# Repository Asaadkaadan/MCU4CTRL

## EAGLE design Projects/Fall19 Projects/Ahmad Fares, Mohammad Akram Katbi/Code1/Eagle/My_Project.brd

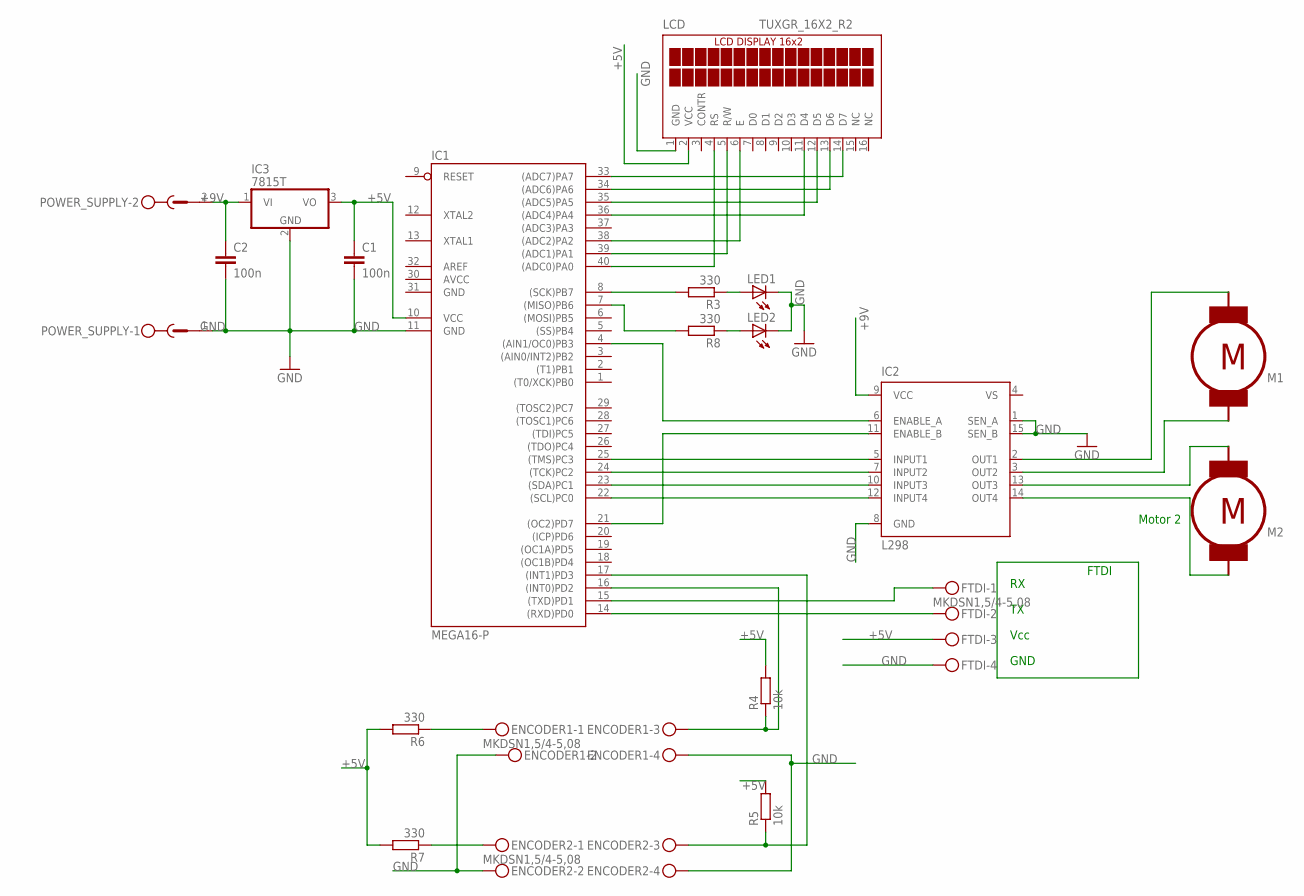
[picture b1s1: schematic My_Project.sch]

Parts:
C1, C2: 100n; C2.5-3
ENCODER1, ENCODER2: MKDSN1,5/4-5,08
FTDI: MKDSN1,5/4-5,08
IC1: MEGA16-P; DIL40; MPN ATMEGA16-16PU
IC2: L298; MULTIWATT-15
IC3: 7815T; TO220H
LCD: TUXGR_16X2_R2
LED1, LED2: LEDLZR181; LZR181
M1, M2: MOTOR_DC_EINFACH_XL; 2PIN
POWER_SUPPLY: MSTBV2
R3, R6, R7, R8: 330; 0207/10
R4, R5: 10k; 0207/10

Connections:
+5V: C1.1, FTDI.3, IC1.10 (VCC), IC3.3 (VO), LCD.2 (VCC), R4.2, R5.2, R6.2, R7.2
+9V: C2.1, IC2.9 (VCC), IC3.1 (VI), POWER_SUPPLY.2
AVCC: IC1.30 (AVCC)
GND: C1.2, C2.2, ENCODER1.2, ENCODER1.4, ENCODER2.2, ENCODER2.4, FTDI.4, IC1.11 (GND), IC1.31 (GND), IC2.1 (SEN_A), IC2.8 (GND), IC2.15 (SEN_B), IC3.2 (GND), LCD.1 (GND), LED1.K (C), LED2.K (C), POWER_SUPPLY.1
unnamed: IC1.33 ((ADC7)PA7), LCD.14 (D7)
unnamed: IC1.34 ((ADC6)PA6), LCD.13 (D6)
unnamed: IC1.35 ((ADC5)PA5), LCD.12 (D5)
unnamed: IC1.36 ((ADC4)PA4), LCD.11 (D4)
unnamed: IC1.38 ((ADC2)PA2), LCD.6 (E)
unnamed: IC1.39 ((ADC1)PA1), LCD.5 (R/W)
unnamed: IC1.40 ((ADC0)PA0), LCD.4 (RS)
unnamed: IC1.4 ((AIN1/OC0)PB3), IC2.6 (ENABLE_A)
unnamed: IC1.21 ((OC2)PD7), IC2.11 (ENABLE_B)
unnamed: IC1.7 ((MISO)PB6), R8.2
unnamed: IC1.25 ((TMS)PC3), IC2.5 (INPUT1)
unnamed: IC1.24 ((TCK)PC2), IC2.7 (INPUT2)
unnamed: IC1.23 ((SDA)PC1), IC2.10 (INPUT3)
unnamed: IC1.22 ((SCL)PC0), IC2.12 (INPUT4)
unnamed: IC1.8 ((SCK)PB7), R3.2
unnamed: LED1.A, R3.1
unnamed: LED2.A, R8.1
unnamed: IC2.2 (OUT1), M1.1 (R1)
unnamed: IC2.3 (OUT2), M1.2 (R2)
unnamed: IC2.13 (OUT3), M2.1 (R1)
unnamed: IC2.14 (OUT4), M2.2 (R2)
unnamed: ENCODER1.1, R6.1
unnamed: ENCODER1.3, IC1.16 ((INT0)PD2), R4.1
unnamed: ENCODER2.3, IC1.17 ((INT1)PD3), R5.1
unnamed: ENCODER2.1, R7.1
RX: FTDI.2, IC1.14 ((RXD)PD0)
TX: FTDI.1, IC1.15 ((TXD)PD1)
VS: IC2.4 (VS)

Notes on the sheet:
Vcc
GND
FTDI
Motor 2

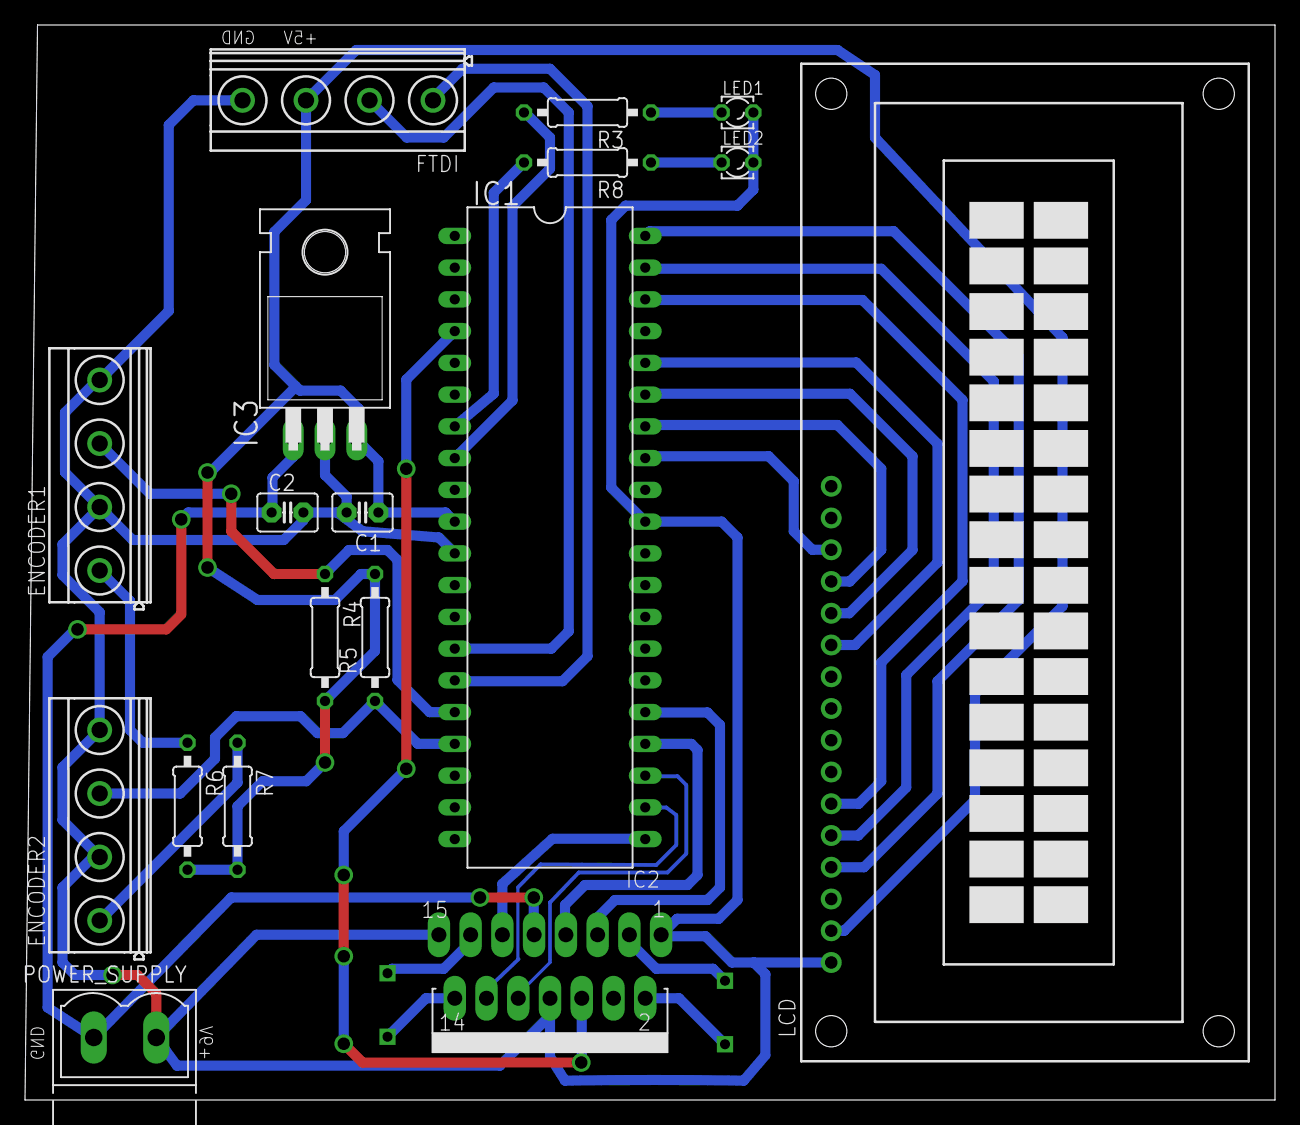
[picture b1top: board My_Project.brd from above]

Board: 2 copper layers, 100.0 x 86.0 mm, 20 parts (0 on the bottom side), 30 nets.

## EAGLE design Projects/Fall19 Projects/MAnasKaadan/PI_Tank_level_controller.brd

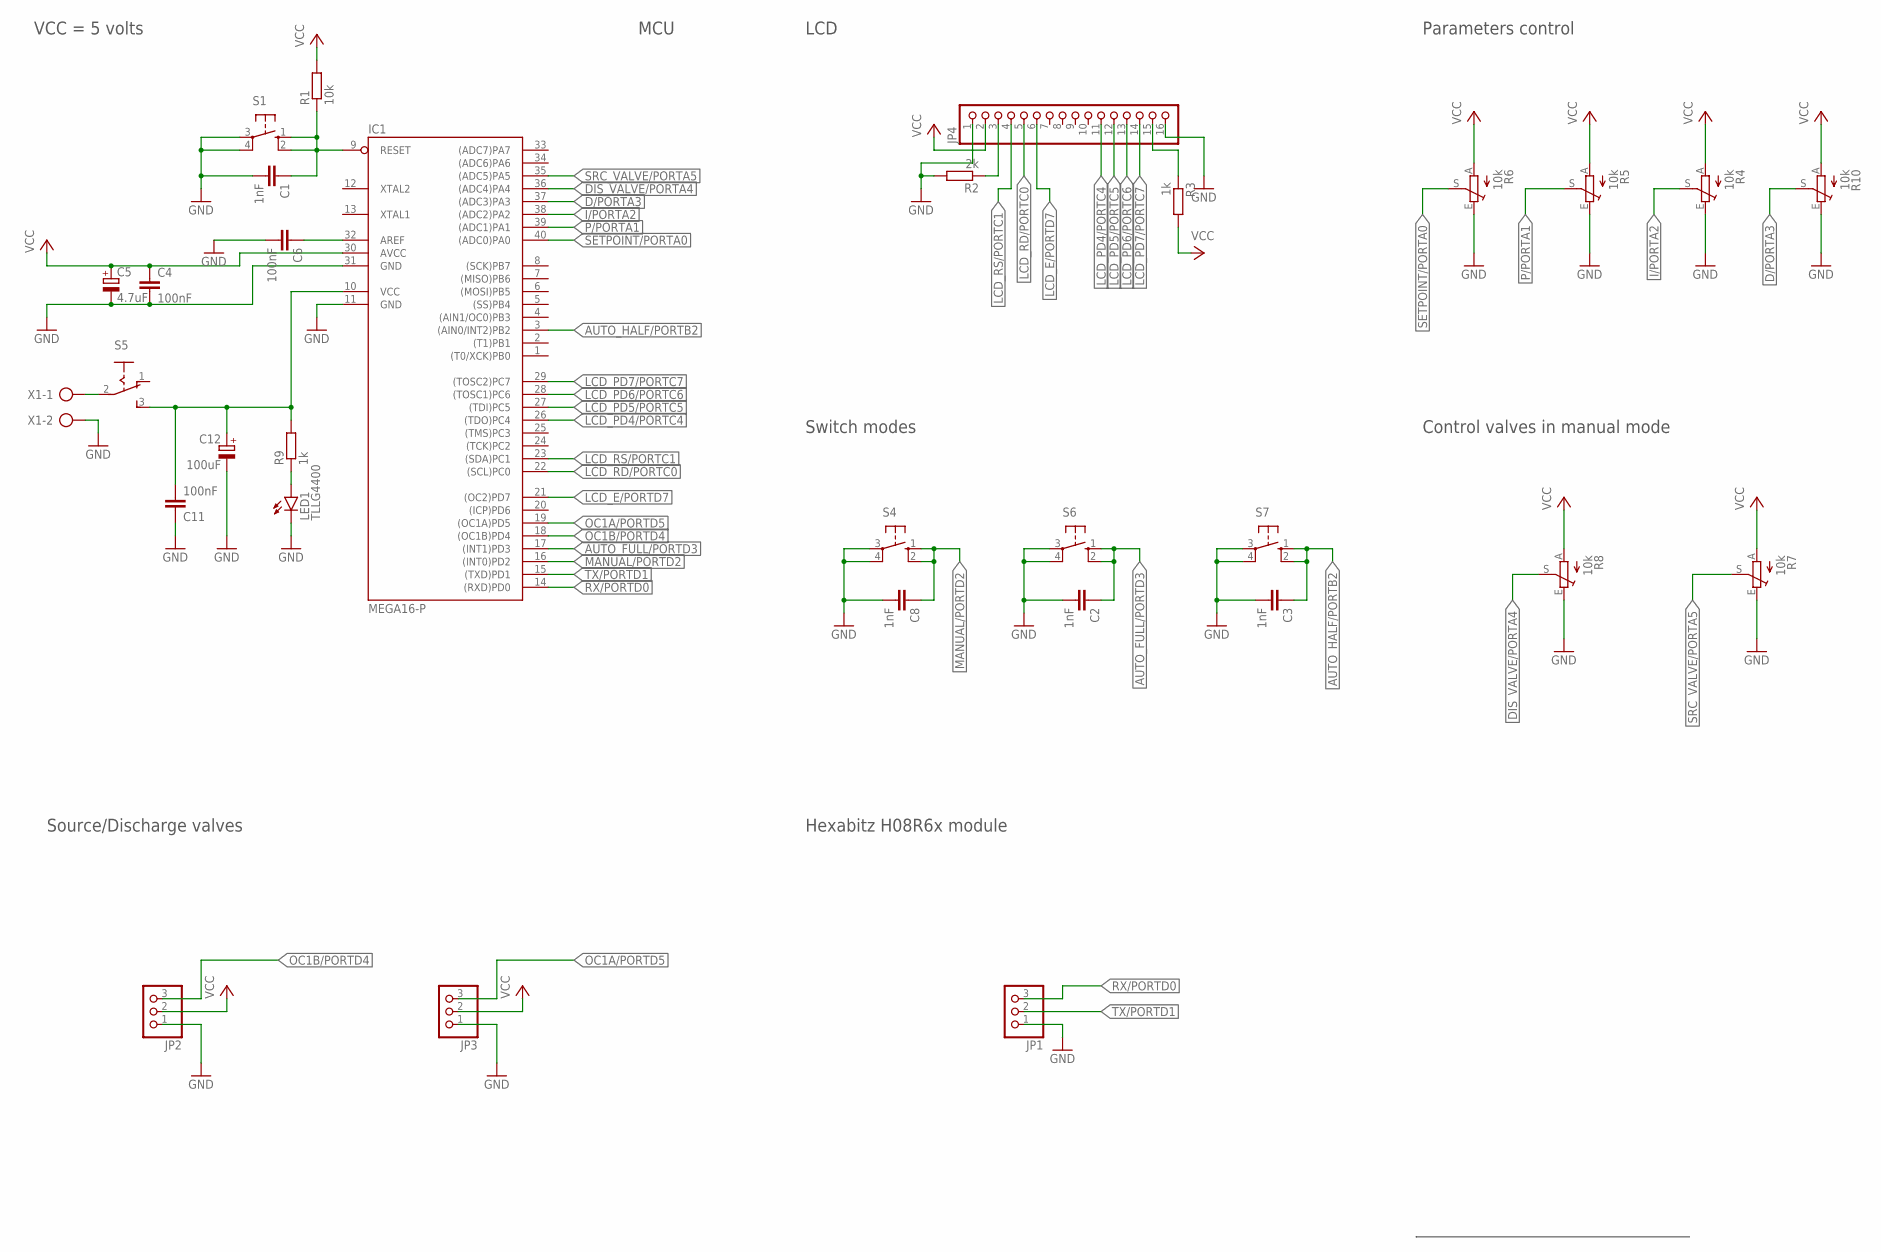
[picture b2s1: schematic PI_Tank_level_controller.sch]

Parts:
C1, C2, C3, C8: 1nF; C025-024X044
C4, C6, C11: 100nF; C025-024X044
C5: 4.7uF; E2,5-6E
C12: 100uF; B45181A
IC1: MEGA16-P; DIL40
JP1, JP2, JP3: PINHD-1X3; 1X03
JP4: PINHD-1X16; 1X16
LED1: TLLG4400; LED3MM
R1: 10k; 0204/7
R2: 2k; 0204/7
R3, R9: 1k; 0204/7
R4, R5, R6, R7, R8, R10: 10k; RJ9W
S1, S4, S6, S7: 10-XX; B3F-10XX
S5: 255SB
X1: AK300/2

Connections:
AUTO_FULL/PORTD3: C2.1, IC1.17 ((INT1)PD3), S6.1 (S), S6.2 (S1)
AUTO_HALF/PORTB2: C3.1, IC1.3 ((AIN0/INT2)PB2), S7.1 (S), S7.2 (S1)
D/PORTA3: IC1.37 ((ADC3)PA3), R10.S
DIS_VALVE/PORTA4: IC1.36 ((ADC4)PA4), R8.S
GND: C1.2, C2.2, C3.2, C4.2, C5.-, C6.2, C8.2, C11.1, C12.-, IC1.11 (GND), IC1.31 (GND), JP1.1, JP2.1, JP3.1, JP4.1, JP4.16, LED1.K (C), R2.2, R4.E, R5.E, R6.E, R7.E, R8.E, R10.E, S1.3, S1.4 (P1), S4.3, S4.4 (P1), S6.3, S6.4 (P1), S7.3, S7.4 (P1), X1.2
I/PORTA2: IC1.38 ((ADC2)PA2), R4.S
LCD_E/PORTD7: IC1.21 ((OC2)PD7), JP4.6
LCD_PD4/PORTC4: IC1.26 ((TDO)PC4), JP4.11
LCD_PD5/PORTC5: IC1.27 ((TDI)PC5), JP4.12
LCD_PD6/PORTC6: IC1.28 ((TOSC1)PC6), JP4.13
LCD_PD7/PORTC7: IC1.29 ((TOSC2)PC7), JP4.14
LCD_RD/PORTC0: IC1.22 ((SCL)PC0), JP4.5
LCD_RS/PORTC1: IC1.23 ((SDA)PC1), JP4.4
MANUAL/PORTD2: C8.1, IC1.16 ((INT0)PD2), S4.1 (S), S4.2 (S1)
unnamed: C1.1, IC1.9 (RESET), R1.1, S1.1 (S), S1.2 (S1)
unnamed: JP4.15, R3.1
unnamed: C6.1, IC1.32 (AREF)
unnamed: JP4.3, R2.1
unnamed: S5.2, X1.1
unnamed: LED1.A, R9.1
OC1A/PORTD5: IC1.19 ((OC1A)PD5), JP3.3
OC1B/PORTD4: IC1.18 ((OC1B)PD4), JP2.3
P/PORTA1: IC1.39 ((ADC1)PA1), R5.S
RX/PORTD0: IC1.14 ((RXD)PD0), JP1.3
SETPOINT/PORTA0: IC1.40 ((ADC0)PA0), R6.S
SRC_VALVE/PORTA5: IC1.35 ((ADC5)PA5), R7.S
TX/PORTD1: IC1.15 ((TXD)PD1), JP1.2
VCC: C4.1, C5.+, C11.2, C12.+, IC1.10 (VCC), IC1.30 (AVCC), JP2.2, JP3.2, JP4.2, R1.2, R3.2, R4.A, R5.A, R6.A, R7.A, R8.A, R9.2, R10.A, S5.3 (S)

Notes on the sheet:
VCC = 5 volts
MCU
LCD
Parameters control
Switch modes
Hexabitz H08R6x module
Source/Discharge valves
Control valves in manual mode

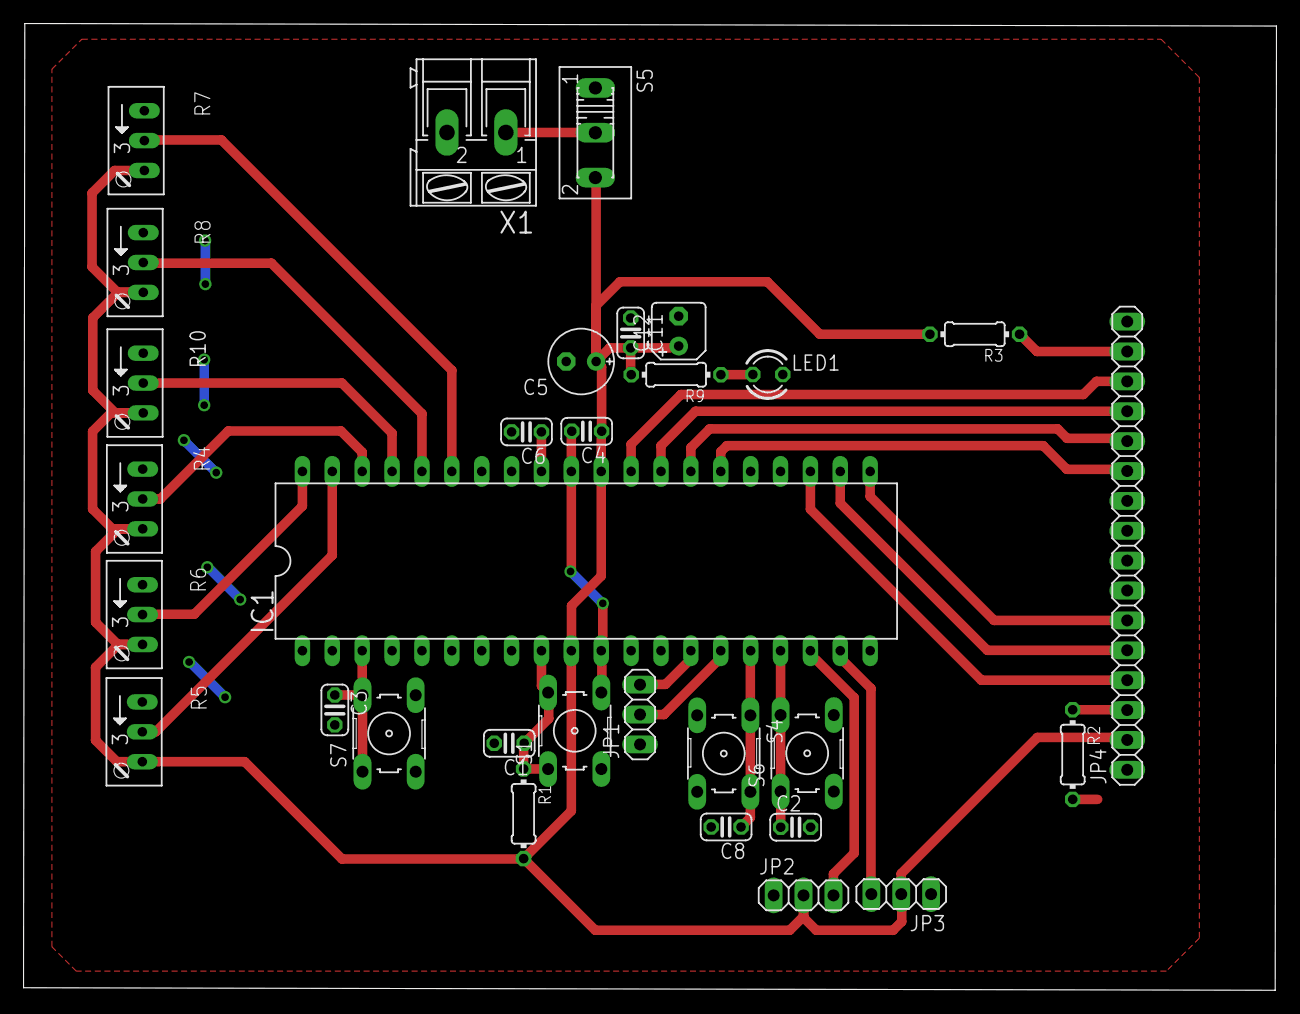
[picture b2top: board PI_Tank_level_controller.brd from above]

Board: 2 copper layers, 106.5 x 82.2 mm, 31 parts (0 on the bottom side), 28 nets.

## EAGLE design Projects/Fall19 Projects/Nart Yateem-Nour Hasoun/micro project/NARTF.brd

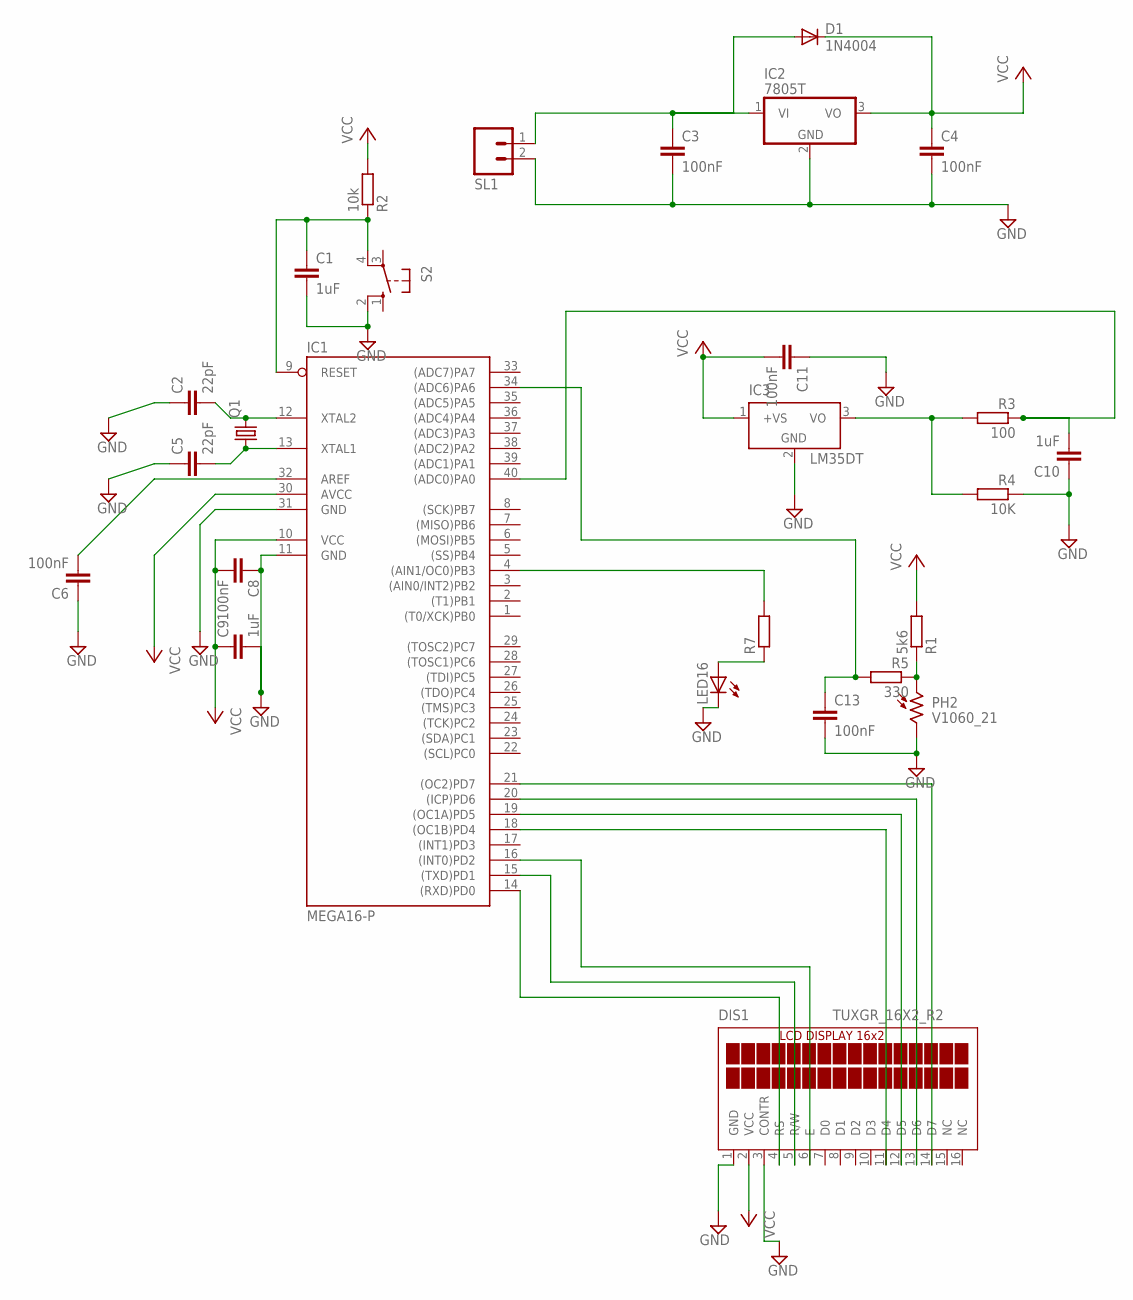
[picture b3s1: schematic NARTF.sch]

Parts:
C1, C9, C10: 1uF; C025-025X050
C2, C5: 22pF; C025-025X050
C3, C4, C6, C8, C11, C13: 100nF; C025-025X050
D1: 1N4004; DO41-10
DIS1: TUXGR_16X2_R2
IC1: MEGA16-P; DIL40
IC2: 7805T; TO220H
IC3: LM35DT; TO220V
LED16: LED3MM
PH2: V1060_21; TO-5_V10
Q1: CRYSTALHC49U70; HC49U70
R1: 5k6; 0207/7
R2: 10k; 0207/7
R3: 100; 0207/7
R4: 10K; 0207/7
R5: 330; 0207/7
R7: R-EU_0207/12; 0207/12
S2: 10-XX; B3F-10XX
SL1: M02; 02P

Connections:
GND: C1.2, C2.1, C3.2, C4.2, C5.1, C6.1, C8.1, C9.2, C10.1, C11.1, C13.2, DIS1.1 (GND), DIS1.3 (CONTR), IC1.11 (GND), IC1.31 (GND), IC2.2 (GND), IC3.2 (GND), LED16.K (C), PH2.2, R4.1, S2.2 (S1), SL1.2
unnamed: C1.1, IC1.9 (RESET), R2.1, S2.4 (P1)
unnamed: IC1.4 ((AIN1/OC0)PB3), R7.2
unnamed: C3.1, D1.A, IC2.1 (VI), SL1.1
unnamed: C2.2, IC1.12 (XTAL2), Q1.2
unnamed: C5.2, IC1.13 (XTAL1), Q1.1
unnamed: C6.2, IC1.32 (AREF)
unnamed: C13.1, IC1.34 ((ADC6)PA6), R5.2
unnamed: LED16.A, R7.1
unnamed: IC3.3 (VO), R3.2, R4.2
unnamed: DIS1.11 (D4), IC1.18 ((OC1B)PD4)
unnamed: C10.2, IC1.40 ((ADC0)PA0), R3.1
unnamed: DIS1.12 (D5), IC1.19 ((OC1A)PD5)
unnamed: DIS1.13 (D6), IC1.20 ((ICP)PD6)
unnamed: PH2.1, R1.1, R5.1
unnamed: DIS1.4 (RS), IC1.14 ((RXD)PD0)
unnamed: DIS1.5 (R/W), IC1.15 ((TXD)PD1)
unnamed: DIS1.6 (E), IC1.16 ((INT0)PD2)
NART-NOUR: DIS1.14 (D7), IC1.21 ((OC2)PD7)

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
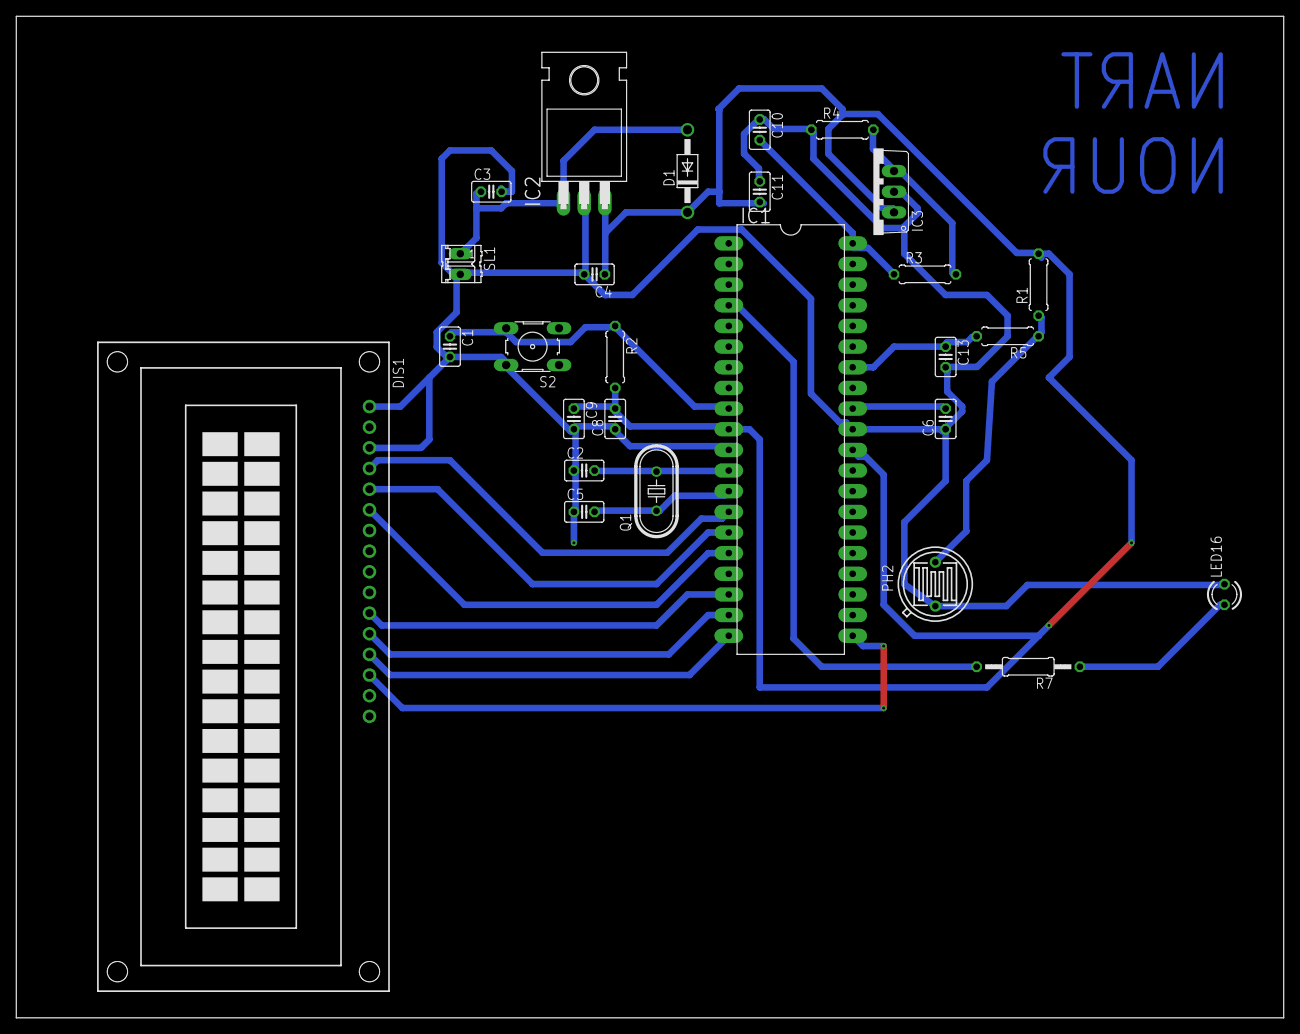
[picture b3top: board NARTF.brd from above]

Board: 2 copper layers, 155.9 x 123.2 mm, 27 parts (0 on the bottom side), 20 nets.

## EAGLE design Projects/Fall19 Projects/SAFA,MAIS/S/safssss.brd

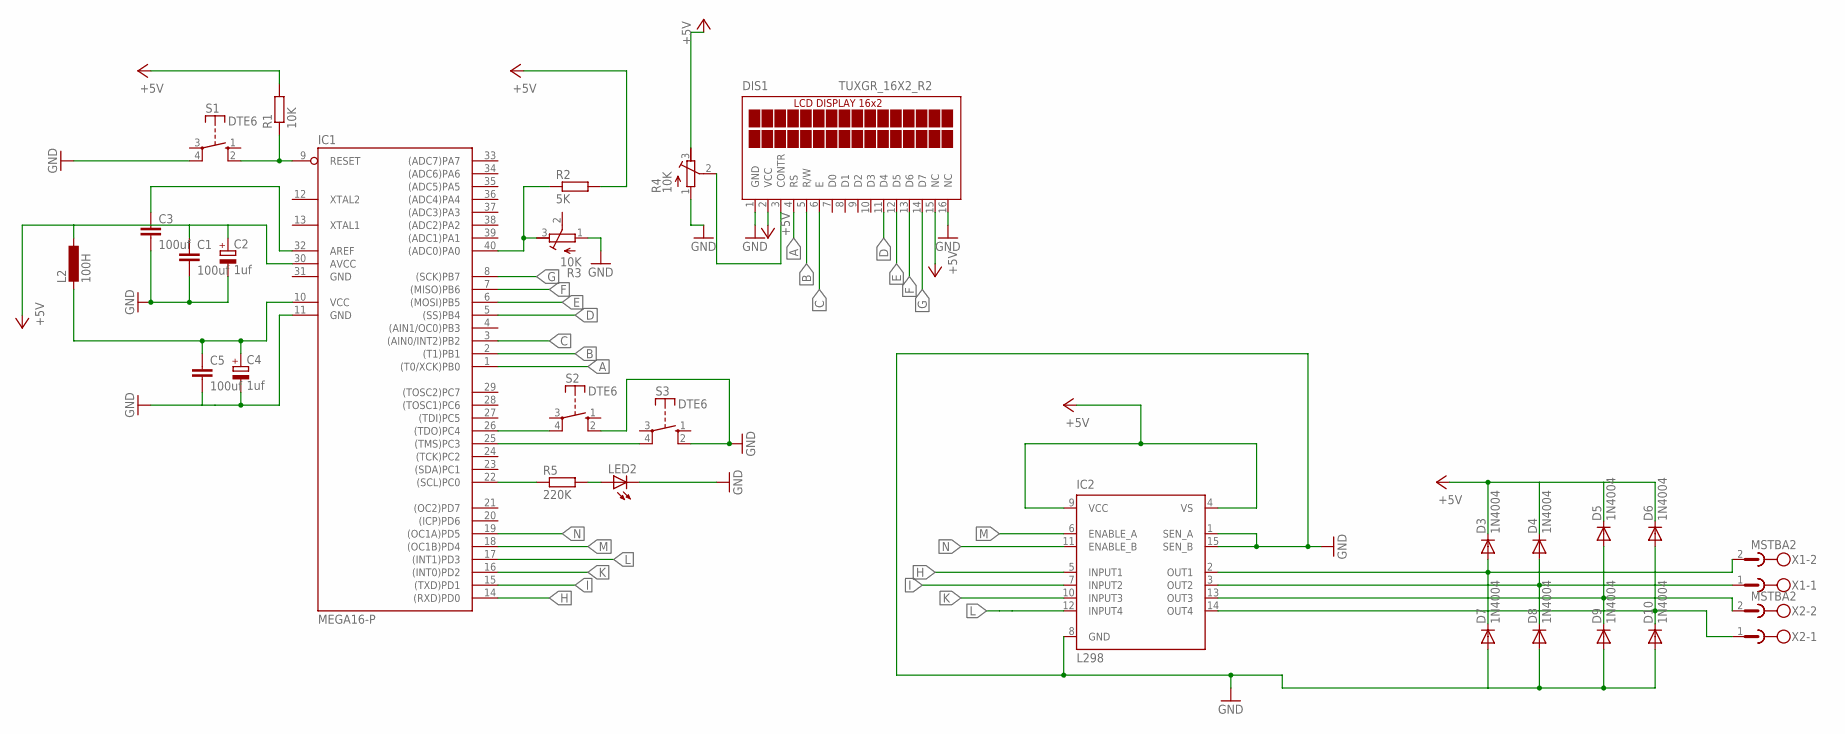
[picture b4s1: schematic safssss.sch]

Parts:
C1, C3, C5: 100uf; C025-024X044
C2, C4: 1uf; B45181A
D3, D4, D5, D6, D7, D8, D9, D10: 1N4004; DO41-10
DIS1: TUXGR_16X2_R2
IC1: MEGA16-P; DIL40
IC2: L298; MULTIWATT-15
L2: 100H; 0204V
LED2: LED3MM
R1: 10K; 0204V
R2: 5K; 0204V
R3, R4: 10K; RTRIM64Z
R5: 220K; 0204V
S1, S2, S3: DTE6
X1, X2: MSTBA2

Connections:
+5V: C1.1, C2.+, D3.C, D4.C, D5.C, D6.C, DIS1.2 (VCC), DIS1.15 (NC), IC1.30 (AVCC), IC2.4 (VS), IC2.9 (VCC), L2.1, R1.2, R2.2, R4.3 (E)
A: DIS1.4 (RS), IC1.1 ((T0/XCK)PB0)
B: DIS1.5 (R/W), IC1.2 ((T1)PB1)
C: DIS1.6 (E), IC1.3 ((AIN0/INT2)PB2)
D: DIS1.11 (D4), IC1.5 ((SS)PB4)
E: DIS1.12 (D5), IC1.6 ((MOSI)PB5)
F: DIS1.13 (D6), IC1.7 ((MISO)PB6)
G: DIS1.14 (D7), IC1.8 ((SCK)PB7)
GND: C1.2, C2.-, C3.2, C4.-, C5.2, D7.A, D8.A, D9.A, D10.A, DIS1.1 (GND), DIS1.16 (NC), IC1.11 (GND), IC1.31 (GND), IC2.1 (SEN_A), IC2.8 (GND), IC2.15 (SEN_B), LED2.K (C), R3.1 (A), R4.1 (A), S1.4, S2.2 (S), S3.2 (S)
H: IC1.14 ((RXD)PD0), IC2.5 (INPUT1)
I: IC1.15 ((TXD)PD1), IC2.7 (INPUT2)
K: IC1.16 ((INT0)PD2), IC2.10 (INPUT3)
L: IC1.17 ((INT1)PD3), IC2.12 (INPUT4)
M: IC1.18 ((OC1B)PD4), IC2.6 (ENABLE_A)
N: IC1.19 ((OC1A)PD5), IC2.11 (ENABLE_B)
unnamed: IC1.9 (RESET), R1.1, S1.2 (S)
unnamed: IC1.40 ((ADC0)PA0), R2.1, R3.3 (E)
unnamed: C3.1, IC1.32 (AREF)
unnamed: C4.+, C5.1, IC1.10 (VCC), L2.2
unnamed: DIS1.3 (CONTR), R4.2 (S)
unnamed: IC1.22 ((SCL)PC0), R5.1
unnamed: LED2.A, R5.2
unnamed: D3.A, D7.C, IC2.2 (OUT1), X1.2
unnamed: D4.A, D8.C, IC2.3 (OUT2), X1.1
unnamed: D5.A, D9.C, IC2.13 (OUT3), X2.2
unnamed: D6.A, D10.C, IC2.14 (OUT4), X2.1
unnamed: IC1.26 ((TDO)PC4), S2.4
unnamed: IC1.25 ((TMS)PC3), S3.4

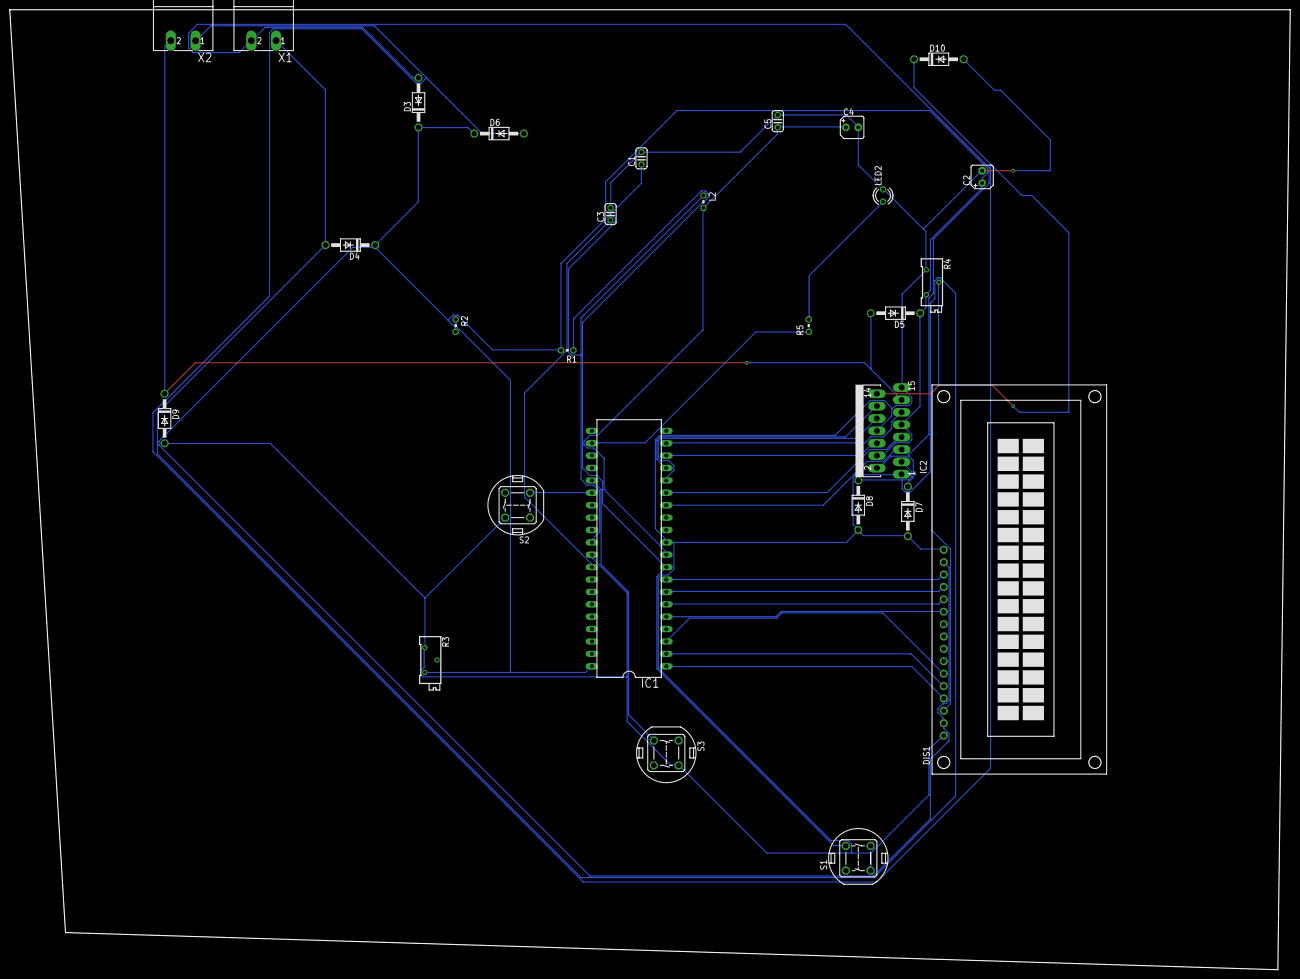
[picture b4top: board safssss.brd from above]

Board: 2 copper layers, 262.6 x 196.8 mm, 28 parts (0 on the bottom side), 28 nets.

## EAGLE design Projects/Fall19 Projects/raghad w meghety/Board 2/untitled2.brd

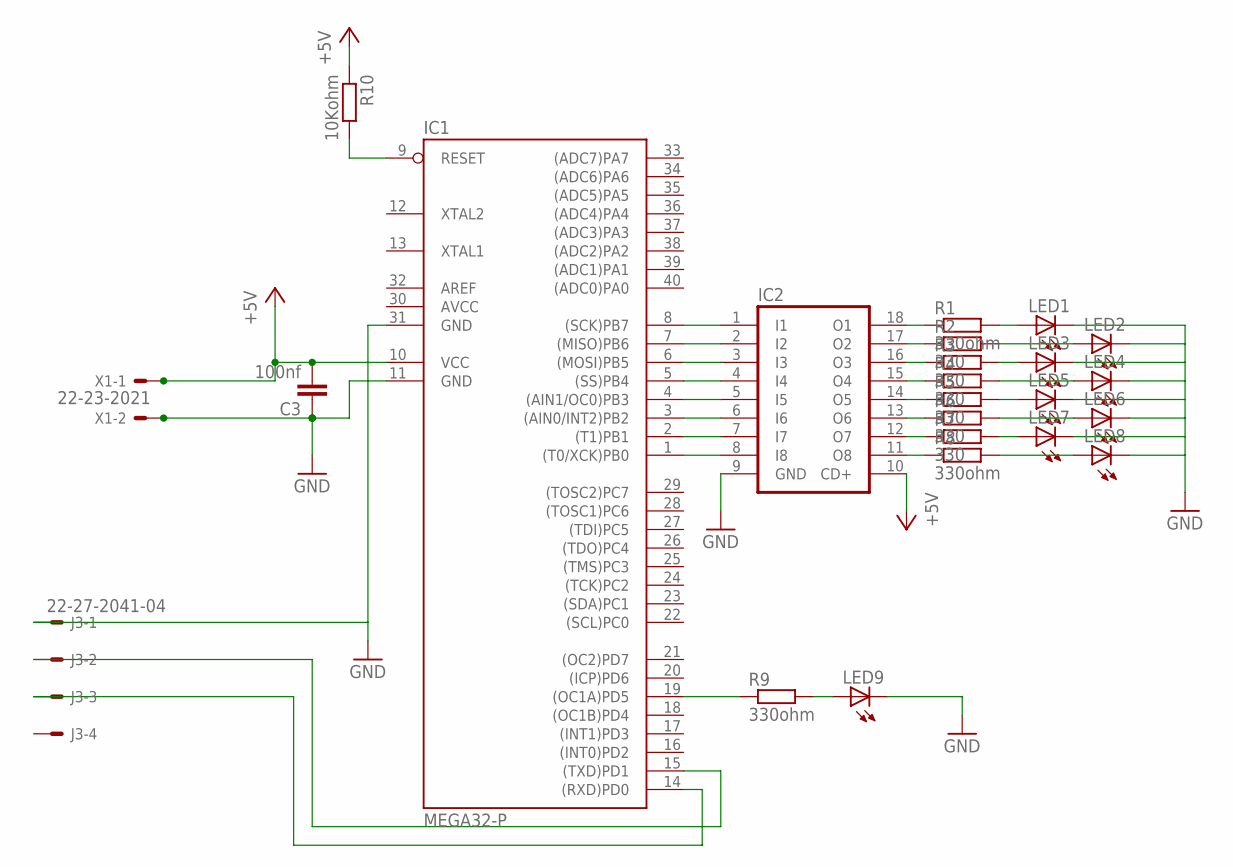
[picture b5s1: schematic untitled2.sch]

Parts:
C3: 100nf; C050-025X075
IC1: MEGA32-P; DIL40
IC2: ULN2803A; DIL18
J3: 22-27-2041-04; 6410-04
LED1, LED2, LED3, LED4, LED5, LED6, LED7, LED8, LED9: LEDIRL80A; IRL80A
R1, R8, R9: 330ohm; 0207/10
R2, R3, R4, R5, R6, R7: 330; 0207/10
R10: 10Kohm; 0207/10
X1: 22-23-2021

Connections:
AVCC: IC1.30 (AVCC)
unnamed: IC1.8 ((SCK)PB7), IC2.1 (I1)
unnamed: IC1.7 ((MISO)PB6), IC2.2 (I2)
unnamed: IC1.6 ((MOSI)PB5), IC2.3 (I3)
unnamed: IC1.5 ((SS)PB4), IC2.4 (I4)
unnamed: IC1.4 ((AIN1/OC0)PB3), IC2.5 (I5)
unnamed: IC1.3 ((AIN0/INT2)PB2), IC2.6 (I6)
unnamed: IC1.2 ((T1)PB1), IC2.7 (I7)
unnamed: IC1.1 ((T0/XCK)PB0), IC2.8 (I8)
unnamed: LED1.A, R1.2
unnamed: LED2.A, R2.2
unnamed: LED3.A, R3.2
unnamed: LED4.A, R4.2
unnamed: LED5.A, R5.2
unnamed: LED6.A, R6.2
unnamed: LED7.A, R7.2
unnamed: LED8.A, R8.2
unnamed: IC1.19 ((OC1A)PD5), R9.1
unnamed: LED9.A, R9.2
unnamed: IC1.9 (RESET), R10.2
unnamed: C3.2, IC1.10 (VCC), IC2.10 (CD+), R10.1, X1.1
unnamed: C3.1, IC1.11 (GND), IC1.31 (GND), IC2.9 (GND), J3.1, LED1.K (C), LED2.K (C), LED3.K (C), LED4.K (C), LED5.K (C), LED6.K (C), LED7.K (C), LED8.K (C), LED9.K (C), X1.2
unnamed: IC1.15 ((TXD)PD1), J3.2
unnamed: IC1.14 ((RXD)PD0), J3.3
unnamed: IC2.18 (O1), R1.1
unnamed: IC2.17 (O2), R2.1
unnamed: IC2.16 (O3), R3.1
unnamed: IC2.15 (O4), R4.1
unnamed: IC2.14 (O5), R5.1
unnamed: IC2.13 (O6), R6.1
unnamed: IC2.12 (O7), R7.1
unnamed: IC2.11 (O8), R8.1

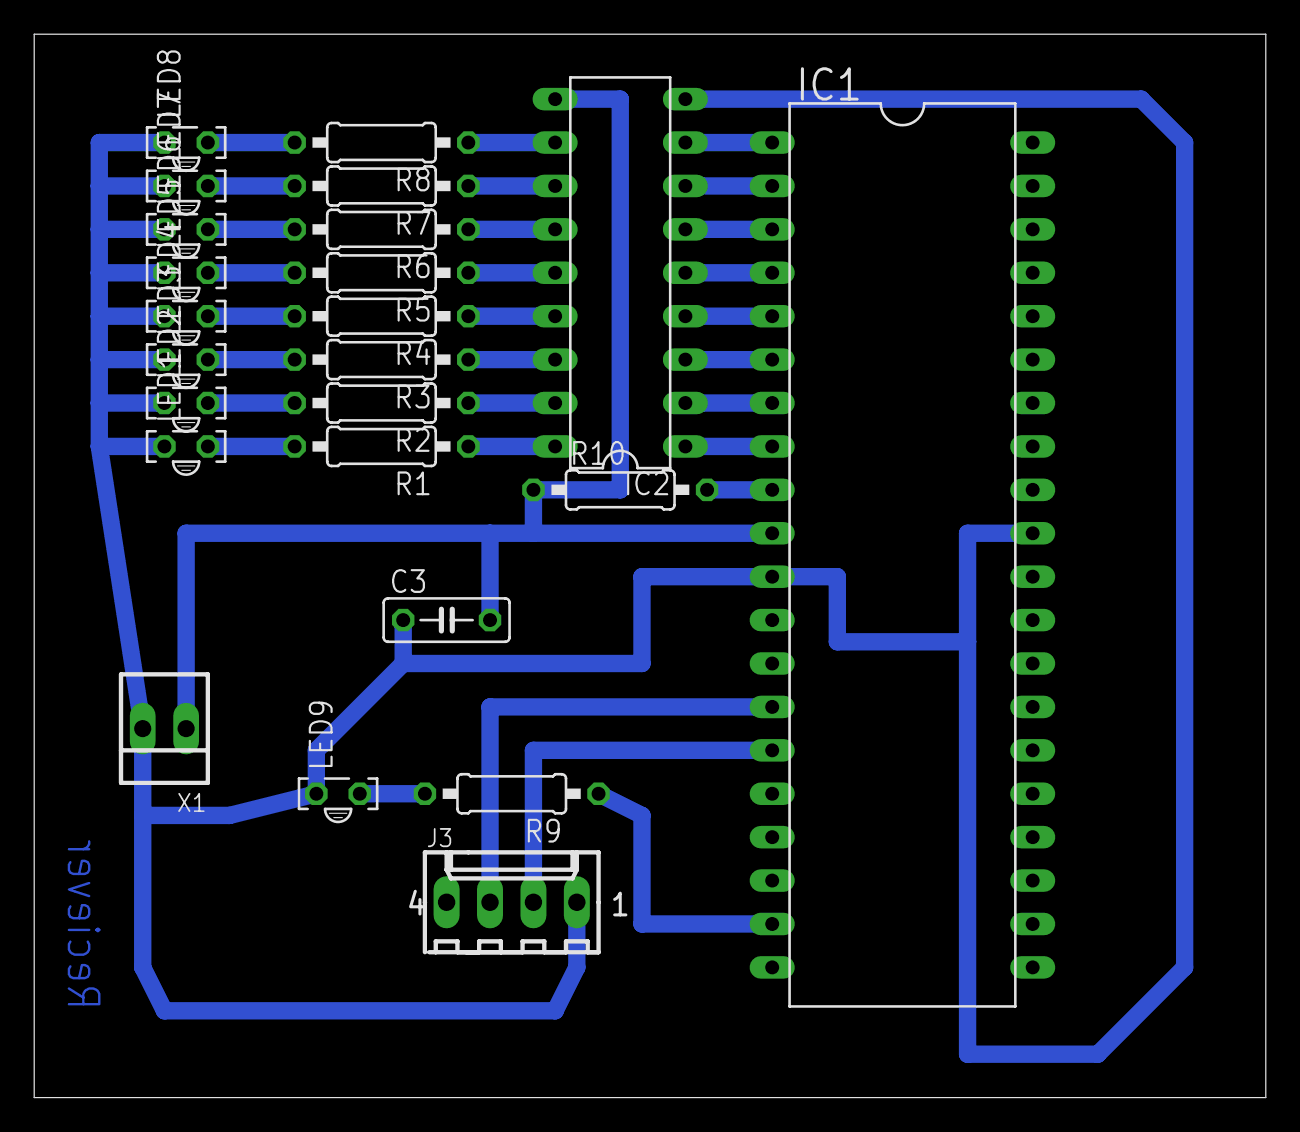
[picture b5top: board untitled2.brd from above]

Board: 2 copper layers, 72.1 x 62.2 mm, 24 parts (0 on the bottom side), 31 nets.

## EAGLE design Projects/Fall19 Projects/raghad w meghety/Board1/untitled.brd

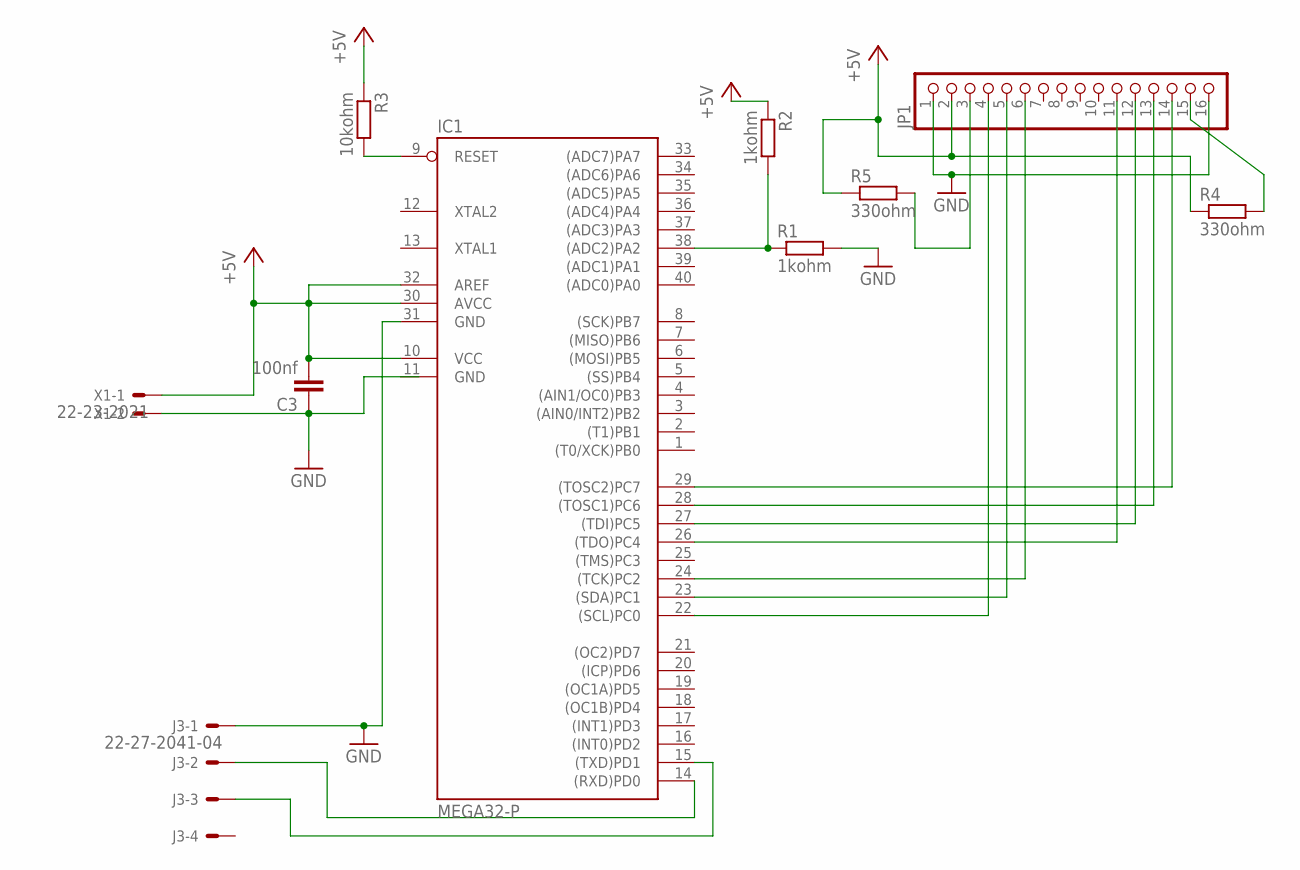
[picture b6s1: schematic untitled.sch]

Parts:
C3: 100nf; C050-025X075
IC1: MEGA32-P; DIL40
J3: 22-27-2041-04; 6410-04
JP1: PINHD-1X16; 1X16
R1, R2: 1kohm; 0207/10
R3: 10kohm; 0207/10
R4, R5: 330ohm; 0207/10
X1: 22-23-2021

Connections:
+5V: C3.2, IC1.10 (VCC), IC1.30 (AVCC), IC1.32 (AREF), JP1.2, R2.1, R3.1, R4.1, R5.1, X1.1
GND: C3.1, IC1.11 (GND), IC1.31 (GND), J3.1, JP1.1, JP1.16, R1.2, X1.2
unnamed: IC1.38 ((ADC2)PA2), R1.1, R2.2
unnamed: IC1.22 ((SCL)PC0), JP1.4
unnamed: IC1.23 ((SDA)PC1), JP1.5
unnamed: IC1.29 ((TOSC2)PC7), JP1.14
unnamed: IC1.28 ((TOSC1)PC6), JP1.13
unnamed: IC1.27 ((TDI)PC5), JP1.12
unnamed: IC1.26 ((TDO)PC4), JP1.11
unnamed: IC1.9 (RESET), R3.2
unnamed: JP1.3, R5.2
unnamed: IC1.24 ((TCK)PC2), JP1.6
unnamed: IC1.14 ((RXD)PD0), J3.2
unnamed: IC1.15 ((TXD)PD1), J3.3
unnamed: JP1.15, R4.2

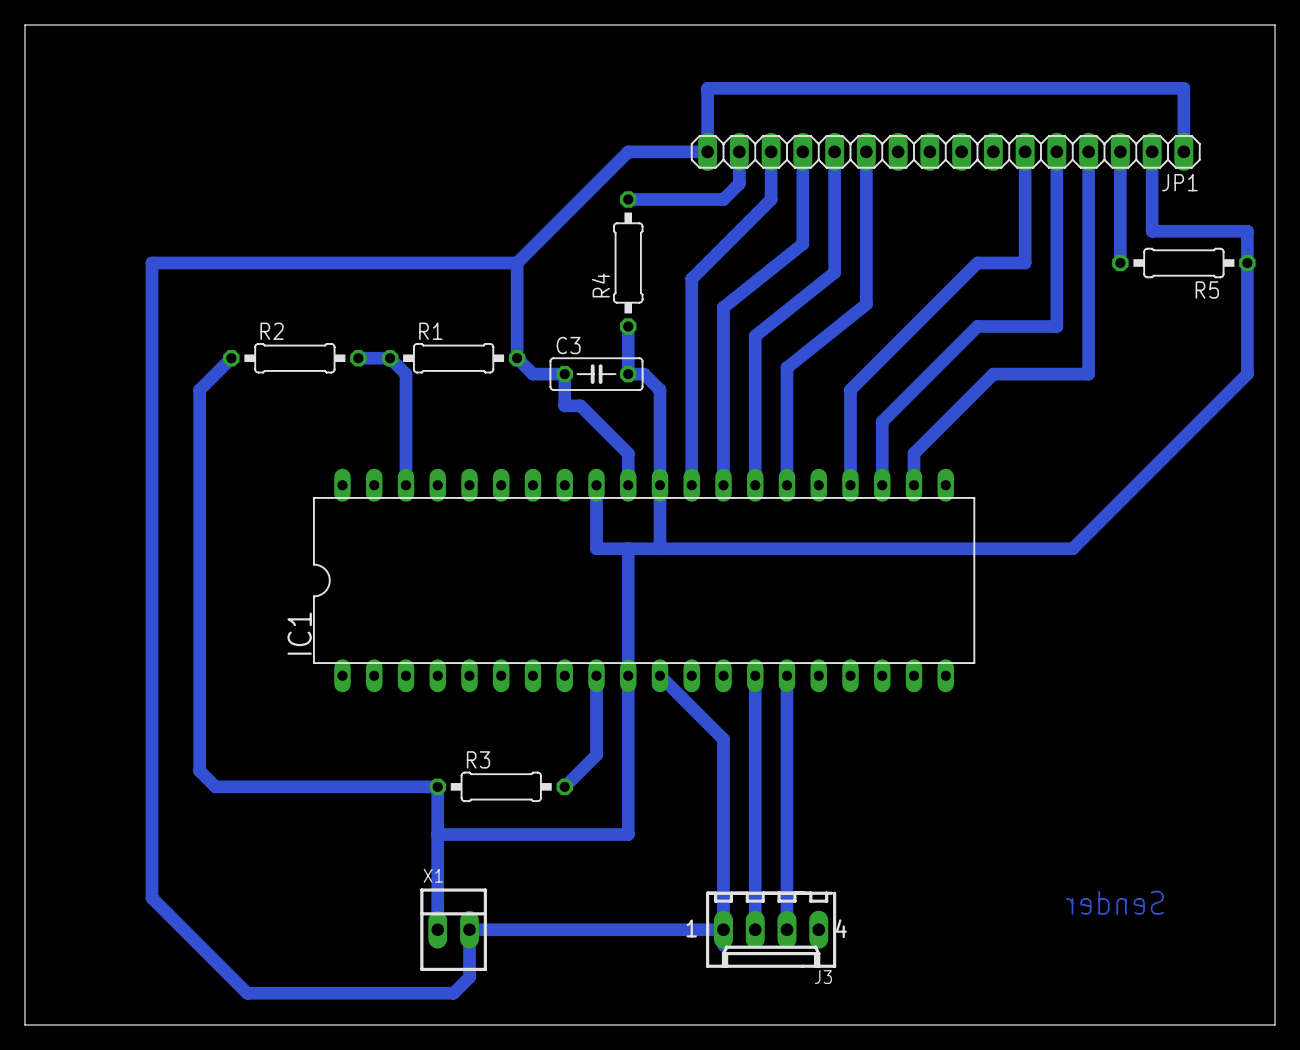
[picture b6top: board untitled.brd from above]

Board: 2 copper layers, 100.0 x 80.0 mm, 10 parts (0 on the bottom side), 15 nets.

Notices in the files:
parts and their libraries:
schule_xl: © by Ralf Stutzenberger
